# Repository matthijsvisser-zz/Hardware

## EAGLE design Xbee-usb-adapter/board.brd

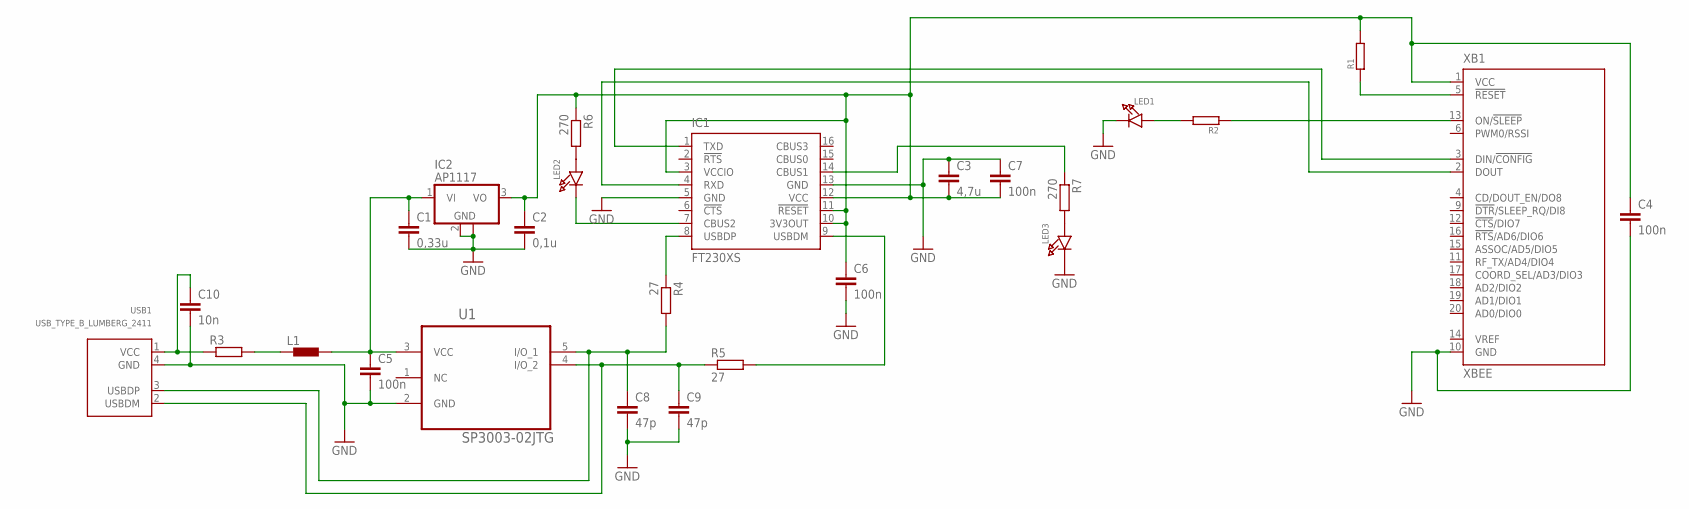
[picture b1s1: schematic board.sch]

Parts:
C1: 0,33u; C0805K
C2: 0,1u; C0805K
C3: 4,7u; C0805K
C4, C5, C6, C7: 100n; C0805K
C8, C9: 47p; C0805K
C10: 10n; C0805K
IC1: FT230XS; SSOP16
IC2: AP1117; SOT223
L1: BLM15HB121SN1; 0402
LED1, LED2, LED3: LED1206; CHIPLED_1206
R1, R2: RESISTOR_0805; 0805
R3: RR1206; R1206
R4, R5: 27; R1206
R6, R7: 270; R1206
U1: SP3003-02JTG; SOT65P220X110-5N
USB1: USB_TYPE_B_LUMBERG_2411
XB1: XBEE

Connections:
GND: C1.2, C2.2, C3.1, C4.2, C5.2, C6.2, C7.1, C8.2, C9.2, C10.2, IC1.5 (GND), IC1.13 (GND), IC2.2 (GND), IC2.4 (GND), LED1.C, LED3.C, U1.2 (GND), USB1.4 (GND), XB1.10 (GND)
unnamed: IC1.4 (RXD), XB1.2 (DOUT)
unnamed: IC1.1 (TXD), XB1.3 (DIN/!CONFIG)
unnamed: C1.1, C5.1, IC2.1 (VI), L1.2, U1.3 (VCC)
unnamed: C10.1, R3.1, USB1.1 (VCC)
unnamed: R1.1, XB1.5 (!RESET)
unnamed: L1.1, R3.2
unnamed: R2.1, XB1.13 (ON/!SLEEP)
unnamed: LED1.A, R2.2
unnamed: IC1.8 (USBDP), R4.1
unnamed: C8.1, R4.2, U1.5 (I/O_1), USB1.3 (USBDP)
unnamed: C9.1, R5.1, U1.4 (I/O_2), USB1.2 (USBDM)
unnamed: C2.1, C3.2, C4.1, C6.1, C7.2, IC1.3 (VCCIO), IC1.10 (3V3OUT), IC1.11 (!RESET), IC1.12 (VCC), IC2.3 (VO), R1.2, R6.1, XB1.1 (VCC)
unnamed: IC1.9 (USBDM), R5.2
unnamed: LED2.A, R6.2
unnamed: IC1.7 (CBUS2), LED2.C
unnamed: IC1.14 (CBUS1), R7.1
unnamed: LED3.A, R7.2

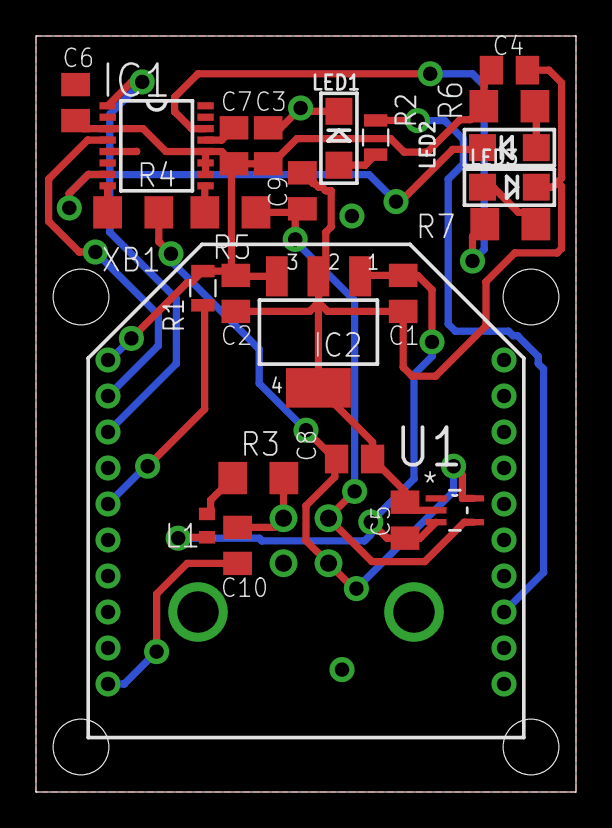
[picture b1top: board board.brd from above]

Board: 2 copper layers, 30.0 x 42.0 mm, 26 parts (1 on the bottom side), 18 nets.

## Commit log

2015-10-15 README
2015-10-15 matthijs kan jij de gerbera maken?
2015-10-15 gerberz

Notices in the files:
parts and their libraries:
microbuilder: This work is placed in the public domain, and may be freely used for commercial and non-commercial work with the following conditions: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
